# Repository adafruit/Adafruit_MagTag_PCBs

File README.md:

## Adafruit MagTag PCB

<a href="http://www.adafruit.com/products/4800"><br/>
Click here to purchase one from the Adafruit shop</a>

PCB files for the Adafruit MagTag.

Format is EagleCAD schematic and board layout
* https://www.adafruit.com/product/4800

### Description

The Adafruit MagTag combines the new ESP32-S2 wireless module and a 2.9" grayscale E-Ink display to make a low-power IoT display that can show data on its screen even when power is removed! The ESP32-S2 is great because it builds on the years of code and support for the ESP32 and also adds native USB support so you can use this board with Arduino or CircuitPython!

New for 2025! After a long break, the MagTag is back in stock, we've found a 2.9" grayscale E-Ink display that replaces the old discontinued ILI0373. The new display has an SSD1680 chip driver and is supported in Arduino and CircuitPython version 10+!

We designed this board to be low-power friendly - with a spot for a 350 or 420 mAh battery and built in battery charging over USB C. During deep sleep, with the NeoPixels and speaker amplifier disabled, we measured 250uA power draw so you can run for a few weeks between charges.

And of course, the Mag in MagTag stands for magnetic. We have four M3 standoffs that will work perfectly with these mini magnet feet. (Originally they're designed for RGB Matrices but they'll do an excellent job here as well). Screw on the feet and you can attach this display to a metallic shelf, fridge, or bench.

Here's the cool hardware we put together:

* ESP32-S2 240MHz Tensilica processor - the next generation of ESP32, now with native USB so it can act like a keyboard/mouse, MIDI device, disk drive, etc!
* WROVER module has FCC/CE certification and comes with 4 MByte of Flash and 2 MByte of PSRAM - you can have huge data buffers
* 2.9" grayscale display with 296x128 pixels. Each pixel can be white, light gray, dark gray or black. Compared to 'tri-color' displays with a red pigment, this display takes a lot less time to update, only about a second instead of 15 seconds!
* USB C power and data connector
* Four RGB side-emitting NeoPixels so you can light up the display with any color or pattern
* Four buttons can be used to wake up the ESP32 from deep-sleep, or select different modes
* Triple-axis accelerometer (LIS3DH) can be used to detect orientation of the display
* Speaker/Buzzer with mini class D amplifier on DAC output A0 can play tones or lo-fi audio clips.
* Front facing light sensor
* STEMMA QT port for attaching all sorts of I2C devices
* Two STEMMA 3 pin JST connectors for attaching NeoPixels, speakers, servos or relays.
* On/Off switch
* Boot and Reset buttons for re-programming

Revision History:

* As of July 22, 2025 – The display has been updated (old one discontinued); it now uses a modern SSD1680 chip instead of the discontinued ILI0373 - we have support in CircuitPython/Python/Arduino for it!
* As of June 17, 2022 - This board may come with a different regulator than AP2112K due to parts shortages. The regulator can provide at least 500mA.
* As of Dec 14, 2020 we're shipping with a different front silkscreen (black not white) Product is otherwise the same

### License

Adafruit invests time and resources providing this open source design, please support Adafruit and open-source hardware by purchasing products from [Adafruit](https://www.adafruit.com)!

Designed by Limor Fried/Ladyada for Adafruit Industries.

Creative Commons Attribution/Share-Alike, all text above must be included in any redistribution.
See license.txt for additional details.

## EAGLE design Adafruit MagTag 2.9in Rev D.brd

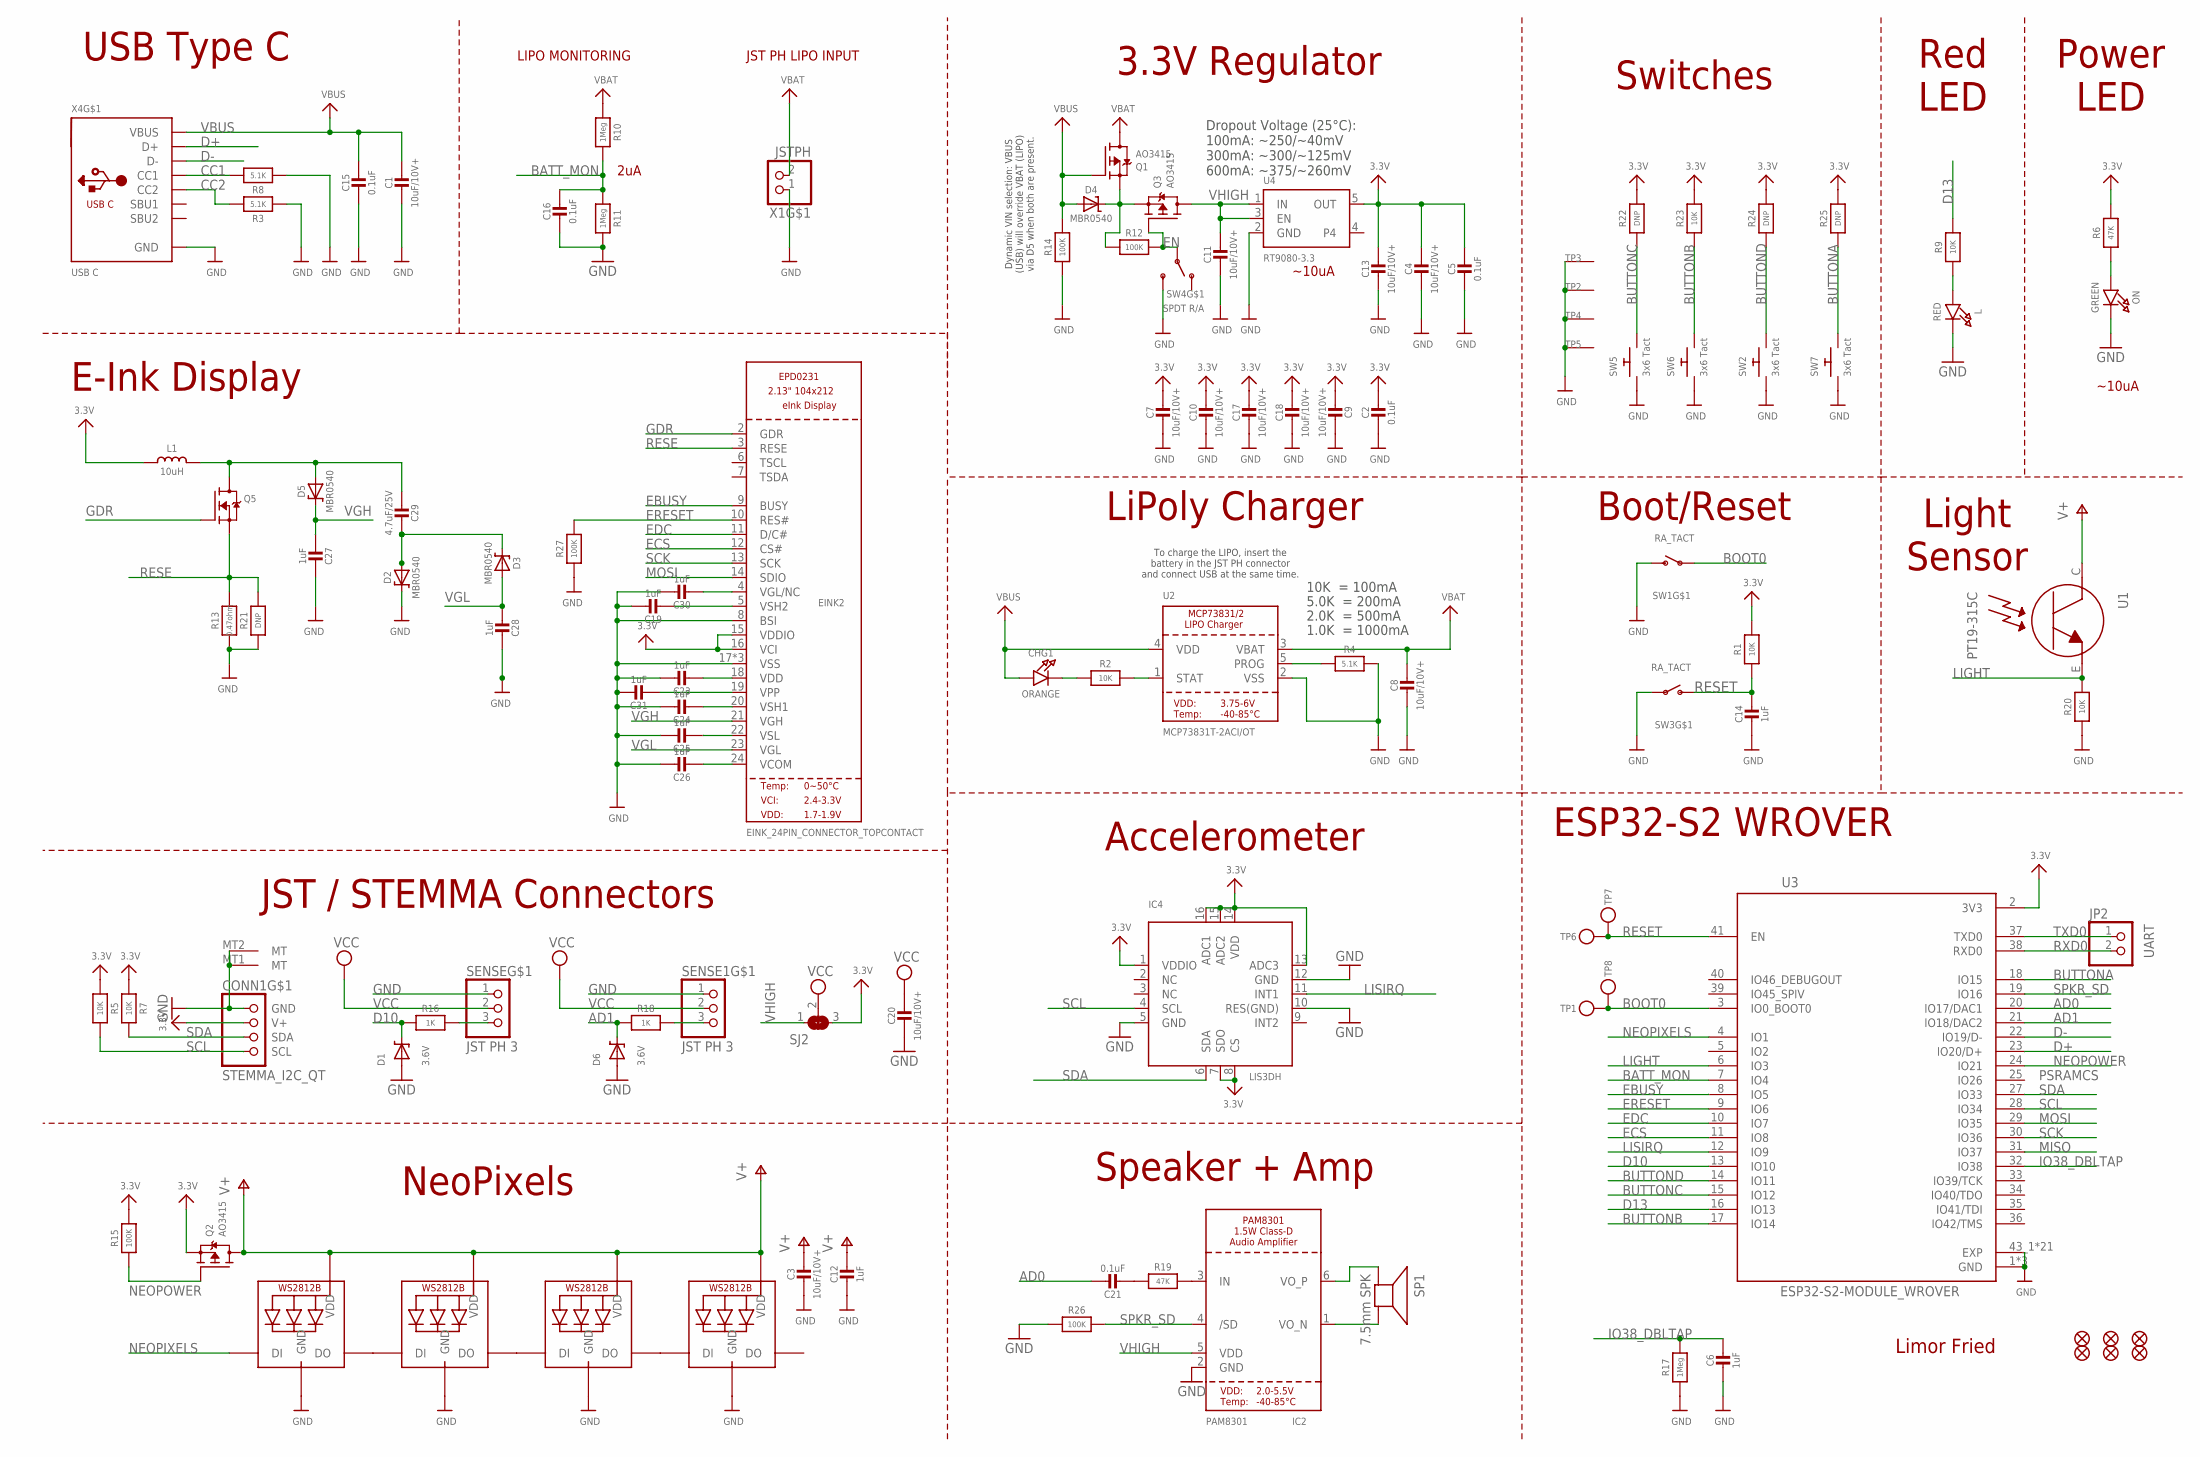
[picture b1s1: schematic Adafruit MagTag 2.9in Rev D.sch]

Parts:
C1, C3, C4, C7, C8, C9, C10, C11, C13, C17, C18, C20: 10uF/10V+; 0805-NO
C2, C5, C15, C16, C21: 0.1uF; 0603-NO
C6, C12, C14: 1uF; 0603-NO
C19, C23, C24, C25, C26, C27, C28, C30, C31: 1uF; 0805-NO
C29: 4.7uF/25V; 0805-NO
CHG1: ORANGE; CHIPLED_0603_NOOUTLINE
CONN1: STEMMA_I2C_QT; JST_SH4
D1, D6: 3.6V; SOD-323
D2, D3, D4, D5: MBR0540; SOD-123
EINK2: EINK_24PIN_CONNECTOR_TOPCONTACT; EINK_24PIN_TOPCONTACT
FID1, FID2, FID3, FID4, FID5, FID6: FIDUCIAL_1MM
IC2: PAM8301; SOT23-6
IC4: LIS3DH; LGA16_3X3MM
JP2: UART; 1X02_ROUND
L: RED; CHIPLED_0603_NOOUTLINE
L1: 10uH; INDUCTOR_4X4MM_NR401
LED2, LED3, LED4, LED5: WS2812B_4020
ON: GREEN; CHIPLED_0603_NOOUTLINE
Q1, Q2, Q3: AO3415; SOT23-R
Q5: IRLML0100; SOT23-3
R1, R2, R5, R7, R9, R20, R23: 10K; 0603-NO
R3, R4, R8: 5.1K; 0603-NO
R6, R19: 47K; 0603-NO
R10, R11, R17: 1Meg; 0603-NO
R12, R14, R15, R26, R27: 100K; 0603-NO
R13: 0.47ohm; 0805_10MGAP
R16, R18: 1K; 0603-NO
R21: DNP; 0805_10MGAP
R22, R24, R25: DNP; 0603-NO
SENSE, SENSE1: JST PH 3; JSTPH3
SJ2: SOLDERJUMPER_2WAY; SOLDERJUMPER_2WAY_OPEN_NOPASTE
SP1: 7.5mm SPK; BUZZER_SMT_7.5MM
SW1, SW3: RA_TACT; SPST_TACTILE_RA
SW2, SW5, SW6, SW7: 3x6 Tact; TACTILE_3X6MM
SW4: SPDT R/A; SPDT_SMT_SSSS811101
TP1, TP6, TP7, TP8: TESTPOINTROUND1.5MMNO; TESTPOINT_ROUND_1.5MM_NO
TP2, TP3, TP4, TP5: SEWTAP_SMTNUTM3; SMT_NUT_3MM
U1: PT19-315C; ALS-PT19-315C
U2: MCP73831T-2ACI/OT; SOT23-5
U3: ESP32-S2-MODULE_WROVER; MODULE_ESP32-S2-WROVER
U4: RT9080-3.3; SOT23-5; JLC_ROTATION 0
X1: JSTPH; JSTPH2_BATT
X4: USB C; USB_C_CUSB31-CFM2AX-01-X

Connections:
3.3V: C2.1, C4.1, C5.1, C7.1, C9.2, C10.1, C13.1, C17.1, C18.1, CONN1.2 (V+), EINK2.15 (VDDIO), EINK2.16 (VCI), IC4.1 (VDDIO), IC4.7 (SDO), IC4.8 (CS), IC4.13 (ADC3), IC4.14 (VDD), IC4.15 (ADC2), IC4.16 (ADC1), L1.P$2 (2), Q2.2 (S), R1.2, R5.1, R6.2, R7.1, R15.2, R22.2, R23.2, R24.2, R25.2, SJ2.3, U3.2 (3V3), U4.5 (OUT)
A1_JST1: R18.1, SENSE1.3
AD0: C21.1, U3.20 (IO17/DAC1)
AD1: D6.C, R18.2, U3.21 (IO18/DAC2)
BATT_MON: C16.1, R10.2, R11.1, U3.7 (IO4)
BOOT0: SW1.1, TP1.P$1, TP8.P$1, U3.3 (IO0_BOOT0)
BUTTONA: R25.1, SW7.P$2, U3.18 (IO15)
BUTTONB: R23.1, SW6.P$2, U3.17 (IO14)
BUTTONC: R22.1, SW5.P$2, U3.15 (IO12)
BUTTOND: R24.1, SW2.P$2, U3.14 (IO11)
CC1: R8.2, X4.A5 (CC1)
CC2: R3.2, X4.B5 (CC2)
D10: D1.C, R16.2, U3.13 (IO10)
D10_JST: R16.1, SENSE.3
D13: R9.2, U3.16 (IO13)
D+: U3.23 (IO20/D+), X4.A6 (D+), X4.B6 (D+)
D-: U3.22 (IO19/D-), X4.A7 (D-), X4.B7 (D-)
EBUSY: EINK2.9 (BUSY), U3.8 (IO5)
ECS: EINK2.12 (CS#), U3.11 (IO8)
EDC: EINK2.11 (D/C#), U3.10 (IO7)
EN: Q3.1 (G), R12.2, SW4.B
ERESET: EINK2.10 (RES#), R27.2, U3.9 (IO6)
GDR: EINK2.2 (GDR), Q5.1 (G)
GND: C1.2, C2.2, C3.2, C4.2, C5.2, C6.2, C7.2, C8.2, C9.1, C10.2, C11.2, C12.2, C13.2, C14.2, C15.2, C16.2, C17.2, C18.2, C19.1, C20.2, C23.1, C24.1, C25.1, C26.1, C27.2, C28.2, C30.1, C31.1, CONN1.1 (GND), CONN1.MT1 (MT), CONN1.MT2 (MT), D1.A, D2.C, D6.A, EINK2.8 (BSI), EINK2.17 (VSS), EINK2.SPRT1 (VSS), EINK2.SPRT2 (VSS), IC2.2 (GND), IC4.5 (GND), IC4.10 (RES(GND)), IC4.12 (GND), L.C, LED2.4 (GND), LED3.4 (GND), LED4.4 (GND), LED5.4 (GND), ON.C, R3.1, R4.2, R8.1, R11.2, R13.2, R14.1, R17.1, R20.1, R21.2, R26.1, R27.1, SENSE.1, SENSE1.1, SW1.2 (S), SW2.P$1, SW3.1, SW4.C (S), SW5.P$1, SW6.P$1, SW7.P$1, TP2.P$1, TP3.P$1, TP4.P$1, TP5.P$1, U2.2 (VSS), U3.1 (GND), U3.26 (GND), U3.42 (GND), U3.43_1 (EXP), U3.43_2 (EXP), U3.43_3 (EXP), U3.43_4 (EXP), U3.43_5 (EXP), U3.43_6 (EXP), U3.43_7 (EXP), U3.43_8 (EXP), U3.43_9 (EXP), U3.43_10 (EXP), U3.43_11 (EXP), U3.43_12 (EXP), U3.43_13 (EXP), U3.43_14 (EXP), U3.43_15 (EXP), U3.43_16 (EXP), U3.43_17 (EXP), U3.43_18 (EXP), U3.43_19 (EXP), U3.43_20 (EXP), U3.43_21 (EXP), U4.2 (GND), X1.1, X4.A1B12 (GND), X4.B1A12 (GND)
IO38_DBLTAP: C6.1, R17.2, U3.32 (IO38)
LIGHT: R20.2, U1.E, U3.6 (IO3)
LISIRQ: IC4.11 (INT1), U3.12 (IO9)
MISO: U3.31 (IO37)
MOSI: EINK2.14 (SDIO), U3.29 (IO35)
unnamed: L.A, R9.1
unnamed: LED2.3 (DO), LED3.1 (DI)
unnamed: ON.A, R6.1
unnamed: CHG1.C, R2.1
unnamed: C21.2, R19.1
unnamed: R2.2, U2.1 (STAT)
unnamed: IC2.3 (IN), R19.2
unnamed: R4.1, U2.5 (PROG)
unnamed: C19.2, EINK2.5 (VSH2)
unnamed: C23.2, EINK2.18 (VDD)
unnamed: C24.2, EINK2.20 (VSH1)
unnamed: LED4.3 (DO), LED5.1 (DI)
unnamed: C29.2, D2.A, D3.C
unnamed: C29.1, D5.A, L1.P$1 (1), Q5.3 (D)
unnamed: C30.2, EINK2.4 (VGL/NC)
unnamed: C31.2, EINK2.19 (VPP)
unnamed: LED3.3 (DO), LED4.1 (DI)
unnamed: IC2.1 (VO_N), SP1.-
unnamed: IC2.6 (VO_P), SP1.+
unnamed: D4.C, Q1.2 (S), Q3.2 (S), R12.1
unnamed: C25.2, EINK2.22 (VSL)
unnamed: C26.2, EINK2.24 (VCOM)
NEOPIXELS: LED2.1 (DI), U3.4 (IO1)
NEOPOWER: Q2.1 (G), R15.1, U3.24 (IO21)
RESE: EINK2.3 (RESE), Q5.2 (S), R13.1, R21.1
RESET: C14.1, R1.1, SW3.2 (S), TP6.P$1, TP7.P$1, U3.41 (EN)
RXD0: JP2.2, U3.38 (RXD0)
SCK: EINK2.13 (SCK), U3.30 (IO36)
SCL: CONN1.4 (SCL), IC4.4 (SCL), R5.2, U3.28 (IO34)
SDA: CONN1.3 (SDA), IC4.6 (SDA), R7.2, U3.27 (IO33)
SPKR_SD: IC2.4 (/SD), R26.2, U3.19 (IO16)
TXD0: JP2.1, U3.37 (TXD0)
V+: C3.1, C12.1, LED2.2 (VDD), LED3.2 (VDD), LED4.2 (VDD), LED5.2 (VDD), Q2.3 (D), U1.C
VBAT: C8.1, Q1.3 (D), R10.1, U2.3 (VBAT), X1.2
VBUS: C1.1, C15.1, CHG1.A, D4.A, Q1.1 (G), R14.2, U2.4 (VDD), X4.A4B9 (VBUS), X4.B4A9 (VBUS)
VCC: C20.1, SENSE.2, SENSE1.2, SJ2.2
VGH: C27.1, D5.C, EINK2.21 (VGH)
VGL: C28.1, D3.A, EINK2.23 (VGL)
VHIGH: C11.1, IC2.5 (VDD), Q3.3 (D), SJ2.1, U4.1 (IN), U4.3 (EN)

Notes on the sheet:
Limor Fried
10K = 100mA
5.0K = 200mA
2.0K = 500mA
1.0K = 1000mA
LIPO MONITORING
To charge the LIPO, insert the battery in the JST PH connector and connect USB at the same time.
JST PH LIPO INPUT
Dynamic VIN selection: VBUS (USB) will override VBAT (LIPO) via D5 when both are present.
Dropout Voltage (25°C): 100mA: ~250/~40mV 300mA: ~300/~125mV 600mA: ~375/~260mV
PSRAMCS
2uA
~10uA
E-Ink Display
LiPoly Charger
Accelerometer
Speaker + Amp
3.3V Regulator
ESP32-S2 WROVER
Switches
Boot/Reset
USB Type C
Light Sensor
Red LED
Power LED
NeoPixels
JST / STEMMA Connectors

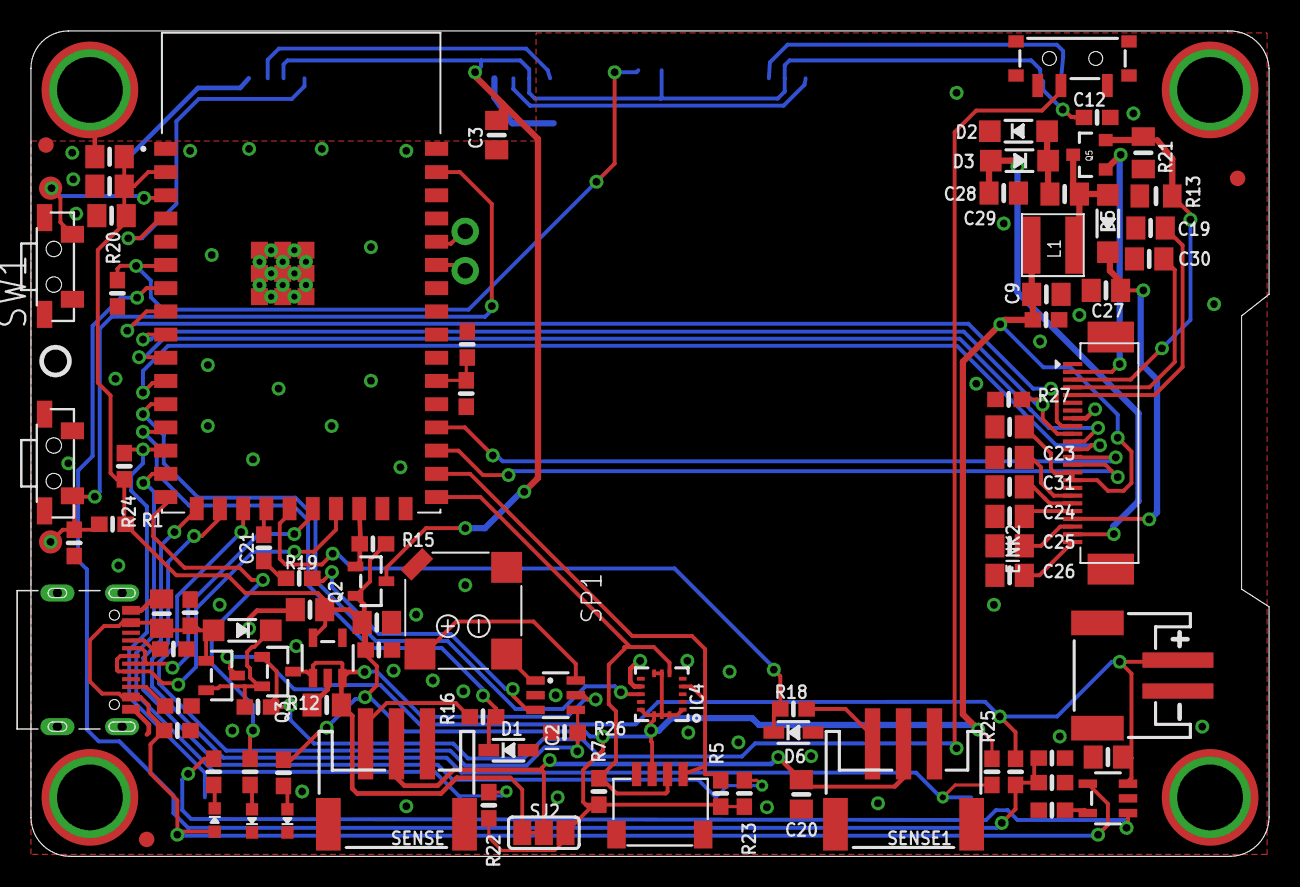
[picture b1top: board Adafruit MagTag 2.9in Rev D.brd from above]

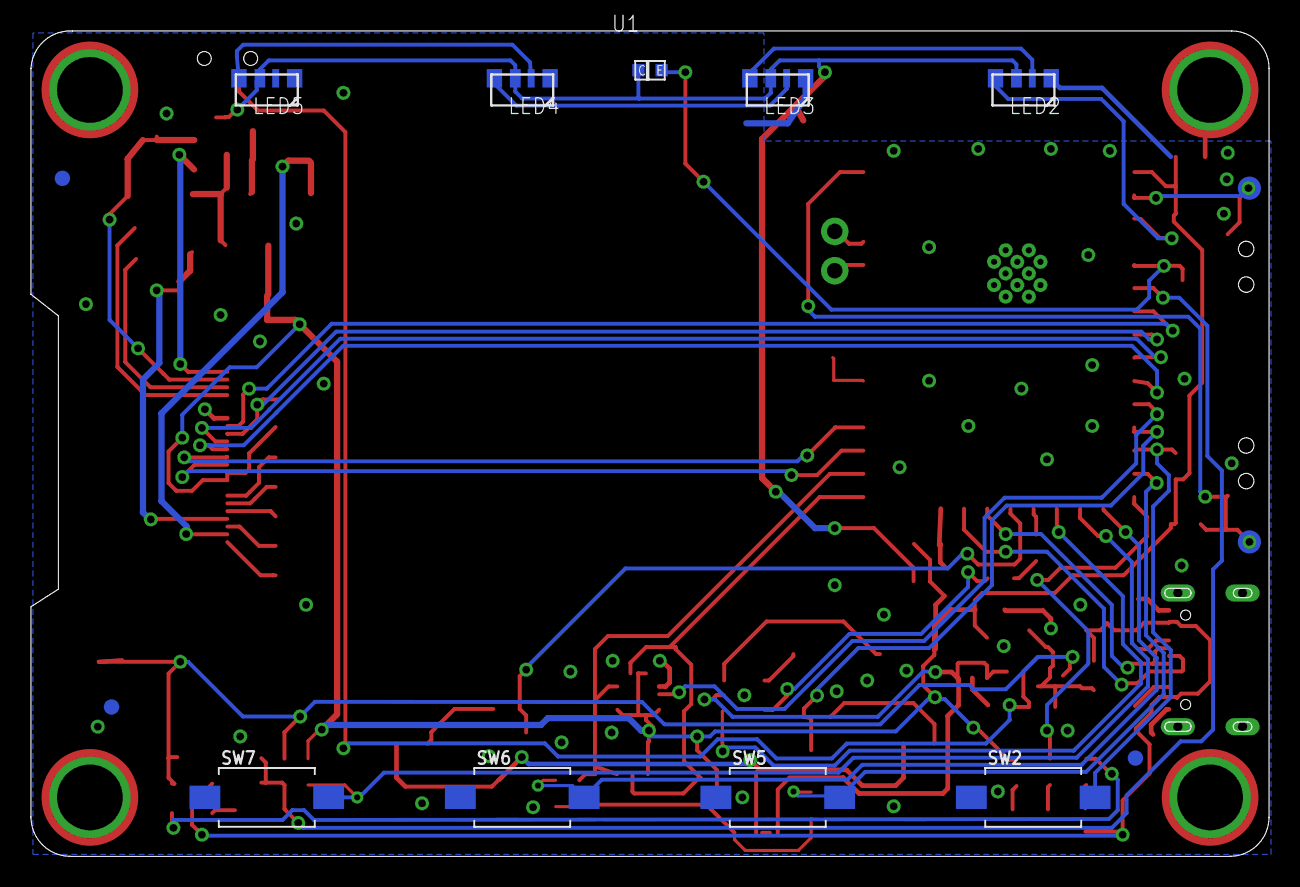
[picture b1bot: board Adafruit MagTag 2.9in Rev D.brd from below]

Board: 2 copper layers, 80.0 x 53.3 mm, 114 parts (15 on the bottom side), 67 nets.

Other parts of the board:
U$15: PCBFEAT-REV-040
U$69: MAGTAG_BOTTOM
U$70: MAGTAG_FRONT

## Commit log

2020-11-09 init
2020-11-10 cookiecutter.
2021-05-12 Add pinout reference PDF
2025-08-04 add 2025 factory reset
2025-08-04 add rev d

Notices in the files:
parts and their libraries:
microbuilder: This work is placed in the public domain, and may be freely used for commercial and non-commercial work with the following conditions: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
